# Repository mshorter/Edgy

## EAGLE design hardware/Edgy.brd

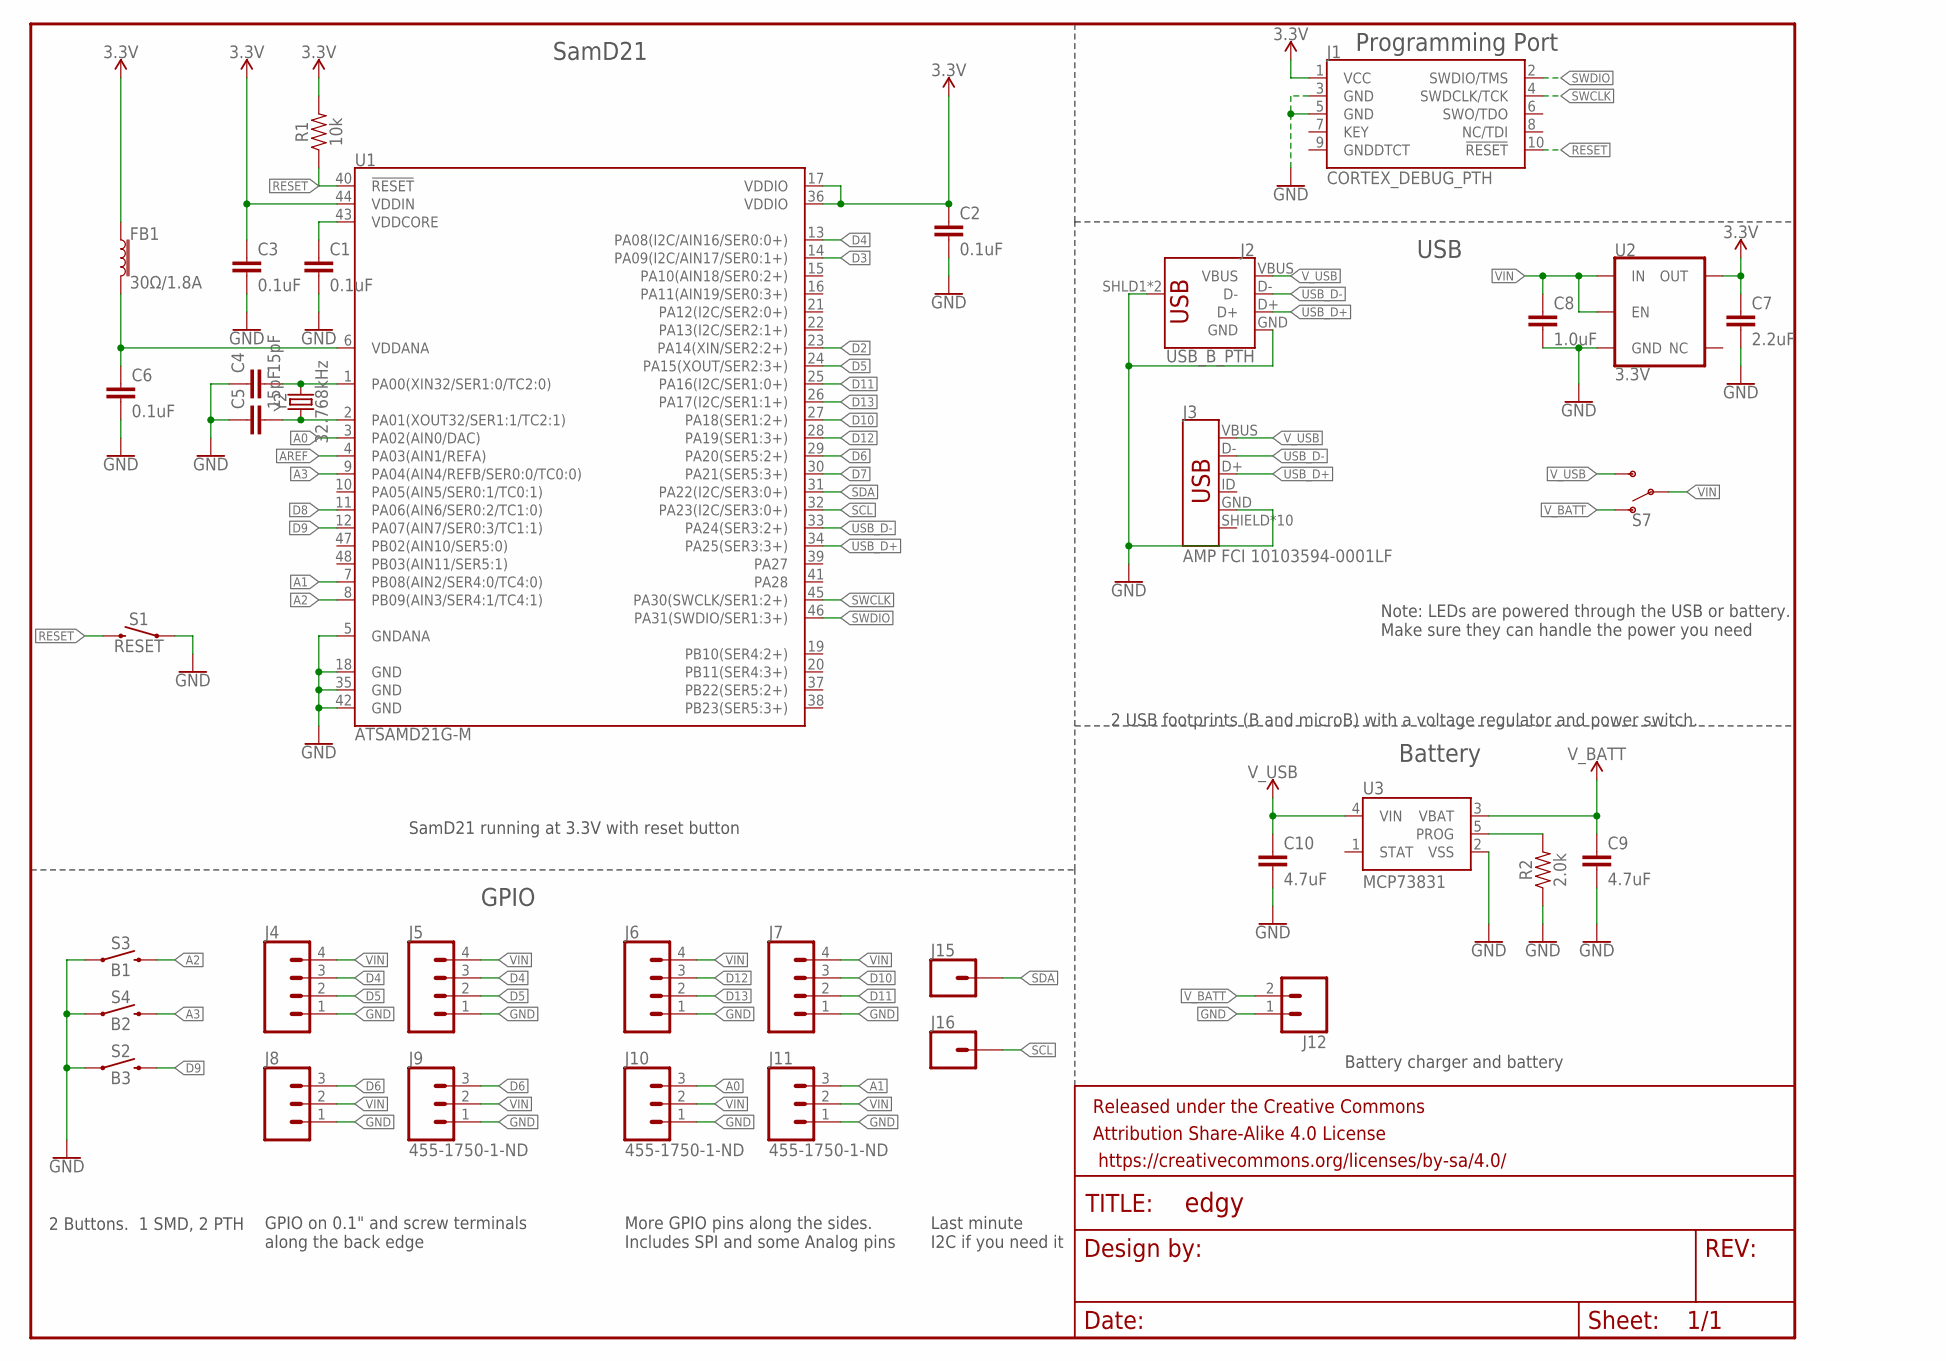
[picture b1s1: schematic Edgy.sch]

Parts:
C1, C2, C3, C6: 0.1uF; 0402
C4, C5: 15pF; 0402
C7: 2.2uF; 0603
C8: 1.0uF; 0402
C9, C10: 4.7uF; 0603
FB1: 30Ω/1.8A; 0603
FRAME1: FRAME-LETTER; CREATIVE_COMMONS
J1: CORTEX_DEBUG_PTH; 2X5-PTH-1.27MM
J2: USB_B_PTH; USB-B-PTH
J3: AMP FCI 10103594-0001LF; USB-MICROB-PTH-MILL
J4: CONN_04SCREW; SCREWTERMINAL-3.5MM-4
J5, J6, J7: CONN_04; 1X04
J8: CONN_03SCREW; SCREWTERMINAL-3.5MM-3
J9, J10, J11: 455-1750-1-ND; 1X03
J12: CONN_02-JST-2MM-SMT; JST-2-SMD
J15, J16: CONN_01; 1X01
R1: 10k; 0603
R2: 2.0k; 0603
S1: RESET; TACTILE_SWITCH_SMD_6.0X3.5MM
S2: B3; TACTILE_SWITCH_SMD_6.0X3.5MM
S3: B1; TACTILE_SWITCH_PTH_RIGHT_ANGLE_KIT
S4: B2; TACTILE_SWITCH_PTH_RIGHT_ANGLE_KIT
S7: SWITCH-SPDT-PTH-11.6X4.0MM; SWITCH_SPDT_PTH_11.6X4.0MM
U1: ATSAMD21G-M; QFN-48
U2: 3.3V; SOT23-5
U3: MCP73831; SOT23-5
Y2: 32.768kHz; CRYSTAL-SMD-3.2X1.5MM

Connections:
3.3V: C2.1, C3.1, C7.1, FB1.1, J1.1 (VCC), R1.2, U1.17 (VDDIO), U1.36 (VDDIO), U1.44 (VDDIN), U2.5 (OUT)
A0: J10.3, U1.3 (PA02(AIN0/DAC))
A1: J11.3, U1.7 (PB08(AIN2/SER4:0/TC4:0))
A2: S3.2, U1.8 (PB09(AIN3/SER4:1/TC4:1))
A3: S4.2, U1.9 (PA04(AIN4/REFB/SER0:0/TC0:0))
AREF: U1.4 (PA03(AIN1/REFA))
D2: U1.23 (PA14(XIN/SER2:2+))
D3: U1.14 (PA09(I2C/AIN17/SER0:1+))
D4: J4.3, J5.3, U1.13 (PA08(I2C/AIN16/SER0:0+))
D5: J4.2, J5.2, U1.24 (PA15(XOUT/SER2:3+))
D6: J8.3, J9.3, U1.29 (PA20(SER5:2+))
D7: U1.30 (PA21(SER5:3+))
D8: U1.11 (PA06(AIN6/SER0:2/TC1:0))
D9: S2.2, U1.12 (PA07(AIN7/SER0:3/TC1:1))
D10: J7.3, U1.27 (PA18(SER1:2+))
D11: J7.2, U1.25 (PA16(I2C/SER1:0+))
D12: J6.3, U1.28 (PA19(SER1:3+))
D13: J6.2, U1.26 (PA17(I2C/SER1:1+))
GND: C1.2, C2.2, C3.2, C4.1, C5.1, C6.2, C7.2, C8.2, C9.2, C10.2, J1.3 (GND), J1.5 (GND), J2.GND, J2.SHLD1 (SHIELD), J2.SHLD2 (SHIELD), J3.GND, J4.1, J5.1, J6.1, J7.1, J8.1, J9.1, J10.1, J11.1, J12.1 (2), R2.1, S1.1, S2.1, S3.1, S4.1, U1.5 (GNDANA), U1.18 (GND), U1.35 (GND), U1.42 (GND), U2.2 (GND), U3.2 (VSS)
unnamed: R2.2, U3.5 (PROG)
unnamed: C6.1, FB1.2, U1.6 (VDDANA)
unnamed: C1.1, U1.43 (VDDCORE)
unnamed: C4.2, U1.1 (PA00(XIN32/SER1:0/TC2:0)), Y2.P$2 (2)
unnamed: C5.2, U1.2 (PA01(XOUT32/SER1:1/TC2:1)), Y2.P$1 (1)
RESET: J1.10 (!RESET), R1.1, S1.2, U1.40 (!RESET!)
SCL: J16.1, U1.32 (PA23(I2C/SER3:0+))
SDA: J15.1, U1.31 (PA22(I2C/SER3:0+))
SWCLK: J1.4 (SWDCLK/TCK), U1.45 (PA30(SWCLK/SER1:2+))
SWDIO: J1.2 (SWDIO/TMS), U1.46 (PA31(SWDIO/SER1:3+))
USB_D+: J2.D+, J3.D+, U1.34 (PA25(SER3:3+))
USB_D-: J2.D-, J3.D-, U1.33 (PA24(SER3:2+))
VIN: C8.1, J4.4, J5.4, J6.4, J7.4, J8.2, J9.2, J10.2, J11.2, S7.2, U2.1 (IN), U2.3 (EN)
V_BATT: C9.1, J12.2 (1), S7.1 (O), U3.3 (VBAT)
V_USB: C10.1, J2.VBUS, J3.VBUS, S7.3 (S), U3.4 (VIN)

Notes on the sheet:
2 USB footprints (B and microB) with a voltage regulator and power switch.
Programming Port
USB
Battery
SamD21
GPIO
SamD21 running at 3.3V with reset button
Battery charger and battery
2 Buttons. 1 SMD, 2 PTH
GPIO on 0.1" and screw terminals along the back edge
More GPIO pins along the sides. Includes SPI and some Analog pins
Last minute I2C if you need it
Note: LEDs are powered through the USB or battery. Make sure they can handle the power you need

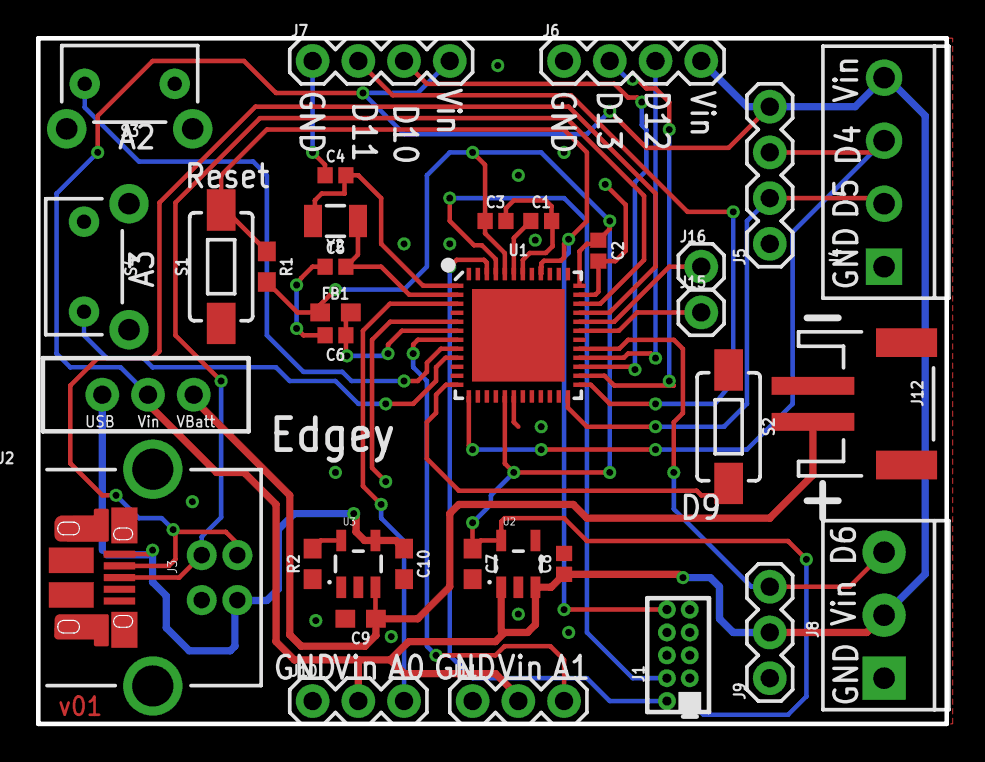
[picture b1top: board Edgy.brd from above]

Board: 2 copper layers, 50.5 x 38.1 mm, 37 parts (1 on the bottom side), 29 nets.

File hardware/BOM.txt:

Qty, PROD_ID, Description
4, CAP-12416, 0.1UF-0402-16V-10%
2, CAP-13063, 15PF-0402-50V-5%
1, CAP-07888, 2.2UF-0603-10V-20%
1, CAP-12417, 1.0UF-0402-16V-10%
2, CAP-08280, 4.7UF-0603-6.3V-(10%)
1, NDUC-13805, FERRITE_BEAD-0603
1, No Prod ID, CORTEX_DEBUG_PTH
1, CONN-08278, USB_B_PTH
1, CONN-13711, USB_MICRO-B_HALF_PTH_MILL
1, RES-00824, 10KOHM-0603-1/10W-1%
1, RES-08296, 2.0KOHM-0603-1/10W-5%
2, SWCH-00815, MOMENTARY-SWITCH-SPST-SMD-6.0X3.5MM
2, CONN-10672, MOMENTARY-SWITCH-SPST-PTH-RIGHT-ANGLE-KIT
1, SWCH-08261, SWITCH-SPDT-PTH-11.6X4.0MM
1, No Prod ID, V_BATT
1, No Prod ID, V_USB
1, IC-13064, ATSAMD21G-M
1, VREG-12457, V_REG_AP2112K-3.3V
1, IC-09995, MCP73831
1, XTAL-13062, CRYSTAL-32.768KHZSMD-3.2X1.5

There are mismatched parts:
FERRITE_BEAD-0603, 30Ω/1.8A
USB_MICRO-B_HALF_PTH_MILL, AMP FCI 10103594-0001LF
MOMENTARY-SWITCH-SPST-SMD-6.0X3.5MM, RESET
MOMENTARY-SWITCH-SPST-SMD-6.0X3.5MM, B3
MOMENTARY-SWITCH-SPST-PTH-RIGHT-ANGLE-KIT, B1
MOMENTARY-SWITCH-SPST-PTH-RIGHT-ANGLE-KIT, B2
SWITCH-SPDT-PTH-11.6X4.0MM, 



12416,13063,7888,12417,8280,13805,8278,13711,824,8296,815,10672,8261,13064,12457,9995,13062,

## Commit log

2018-09-07 Initial Board Files
    Adding initial board files as well as BOM and Assembly guide

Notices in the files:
parts and their libraries:
SparkFun-Capacitors: Licensing: Creative Commons ShareAlike 4.0 International - https://creativecommons.org/licenses/by-sa/4.0
SparkFun-Aesthetics: Released under the Creative Commons Attribution Share-Alike 4.0 License
SparkFun-Aesthetics: https://creativecommons.org/licenses/by-sa/4.0
